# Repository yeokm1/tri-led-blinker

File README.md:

# tri-led-blinker

A "simple" blinking gift for somebody. Has On-Off switch and a button to change the order of blinking.

Blink orders:

1. Forward
2. Reverse
3. Twice forward
4. Twice reverse
5. All

##Software

1. Arduino 1.6.5 IDE
2. [Custom Lowpower library to support ATTiny85 by johnnie502](https://github.com/johnnie502/Low-Power/)

##Hardware

##Prototype

Front view with all LEDs lit

Back view

###Demo video on Youtube

###Parts used that are different from PCB design
1. [Adafruit LED Sequin (Ruby Red)](https://www.adafruit.com/products/1755)
2. [Adafruit LED Sequin (Emerald Green)](https://www.adafruit.com/products/1756)
3. [Adafruit LED Sequin (Royal Blue)](https://www.adafruit.com/products/1757)
4. [Adafruit USB Micro-B Breakout Board](https://www.adafruit.com/products/1833)
5. [Adafruit Perma-Proto Half-sized Breadboard PCB - Single](https://www.adafruit.com/products/1609)

## Proposed PCB Design

###PCB Design software and addons used

1. Eagle 7.3.0: I use Standard but Light should still be able to open/modify the files.
2. Seeed OPL libraries: Button, Connector, Diode (in pcb libraries folder)
2. Seeedstudio Design Rule Check for 2 layers (in repo as `SeeedStudio_2layer_DRU_no_angle_20140221.dru`)
3. Seeed Gerber Generater 2-layer board (in repo as `Seeed_Gerber_Generater_2-layer.cam`)

###Schematic drawings

Images are exported from Eagle at 600dpi.

The copper pour is connected to ground

###Parts required

1. JP1 and JP2: Pin header stand-in for [Adafruit Trinket 3V](https://www.adafruit.com/products/1500)
2. J1: SMD Micro-USB connector: Seeed OPL part 3400150P1
3. S1: [SPDT slide switch from Adafruit](https://www.adafruit.com/products/805). Others will work too
4. K1: Push button: Seeed OPL part 3110040P1
5. JP3 and JP4: Pin header stand-in for [Adafruit Pro Trinket LiIon/LiPoly Backpack Add-On](https://www.adafruit.com/products/2124)
6. D1: 0603 SMD Diffused-Red LED 1.7V-2.2V, 25mA: Seeed OPL part 0330020P1
7. D2: 0603 SMD Clear-Green LED 2.75V-3.95V , 25mA: Seeed OPL part 0330010P1
8. D2: 0603 SMD Clear-Blue LED 2.5V-3.1V , 25mA: Seeed OPL part 0330060P1
9. R1: Through-hole resistor 0.25W for red LED : Undetermined
10. R2: Through-hole resistor 0.25W for green LED : Undetermined
11. R3: Through-hole resistor 0.25W for blue LED : Undetermined

###PCB fabrication

PCB fabrication is currently done by [Seeedstudio](https://www.seeedstudio.com/service/index.php?r=pcb) based on the following settings. Remember to consult the [order submission guidelines](http://support.seeedstudio.com/knowledgebase/articles/422482-fusion-pcb-order-submission-guidelines) before submitting. Use the provided Gerber generator to produce the Gerber files.

Seeedstudio requires the following gerber files to be zipped up for submission:

1. Top Layer: pcbname.GTL
2. Top Solder Mask: pcbname.GTS
3. Top Silkscreen: pcbname.GTO
4. Bottom Layer: pcbname.GBL
5. Bottom Solder Mask﻿: pcbname.GBS
6. Bottom silkscreen: pcbname.GBO
7. Board Outline:pcbname.GML/GKO
8. Drills: pcbname.TXT
9. Inner Layer: pcbname.GL2(for 4 layer)
10. Inner Layer: pcbname.GL3(for 4 layer)

The zip file has been uploaded to the Releases section.

####My Fabrication Settings: 

1. Layer: 2
2. PCB Dimension: 5cm Max * 10cm Max
3. PCB Thickness: 1.2mm
4. PCB Qty: 10
5. PCB Color: Black (+US$20, expensive but I like Black)
6. Surface Finish: Hasl(Lead Free)
7. Copper weight: 1oz
8. Panalized PCBs: 1
9. Expedited Option: No
10. PCB Stencil: Unchecked

####PCB assembly:

Just use the provided `BOM File for Seeedstudio.csv`. I opted to do the assembly for only 5 pieces in case there are issues and I have to solder myself.

###Letters
I 3D-printed the letters based on the STL files obtained from [thingverse](http://www.thingiverse.com/thing:15198).

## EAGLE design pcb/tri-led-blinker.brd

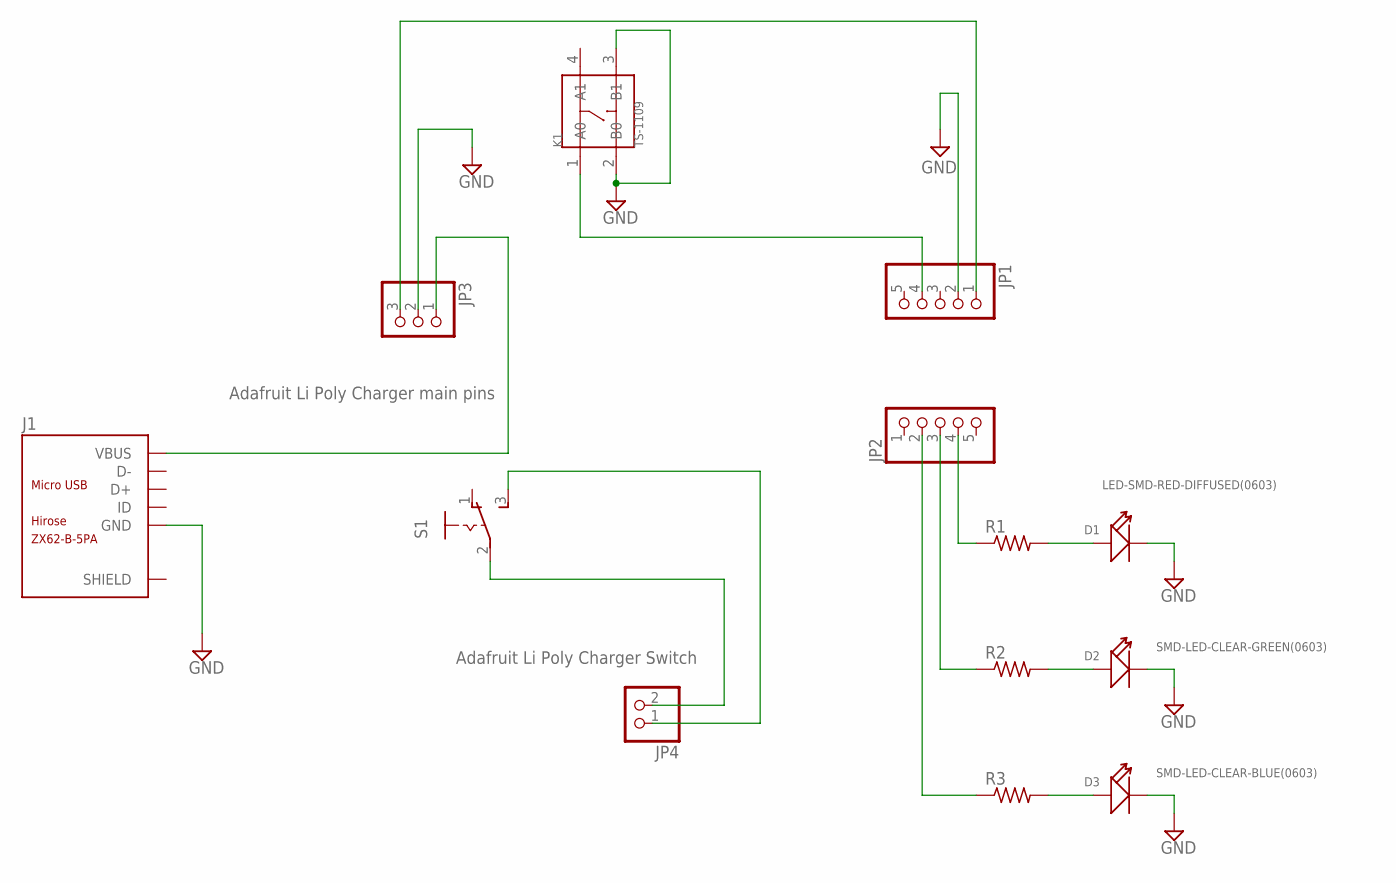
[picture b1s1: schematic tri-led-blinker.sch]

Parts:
D1: LED-SMD-RED-DIFFUSED(0603); LED-0603
D2: SMD-LED-CLEAR-GREEN(0603); LED-0603
D3: SMD-LED-CLEAR-BLUE(0603); LED-0603
J1: MICRO-USB-SMD(ZX62-B-5PA); MICRO-USB5+6P-SMD-0.65-AB
JP1, JP2: PINHD-1X5; 1X05
JP3: Adafruit Li Poly Charger main pins; 1X03
JP4: Adafruit Li Poly Charger Switch; 1X02
K1: TS-1109; SW4-6.0X6.0X5.0MM
R1, R2, R3: R-US_0207/7; 0207/7
S1: M251

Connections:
GND: D1.-, D2.-, D3.-, J1.5 (GND), JP1.2, JP3.2, K1.2 (B0), K1.3 (B1)
unnamed: D1.+, R1.2
unnamed: JP4.2, S1.2
unnamed: JP4.1, S1.3 (S)
unnamed: D2.+, R2.2
unnamed: JP1.4, K1.1 (A0)
unnamed: JP2.2, R3.1
unnamed: D3.+, R3.2
unnamed: JP2.4, R1.1
unnamed: JP1.1, JP3.3
unnamed: JP2.3, R2.1
VBUS: J1.1 (VBUS), JP3.1

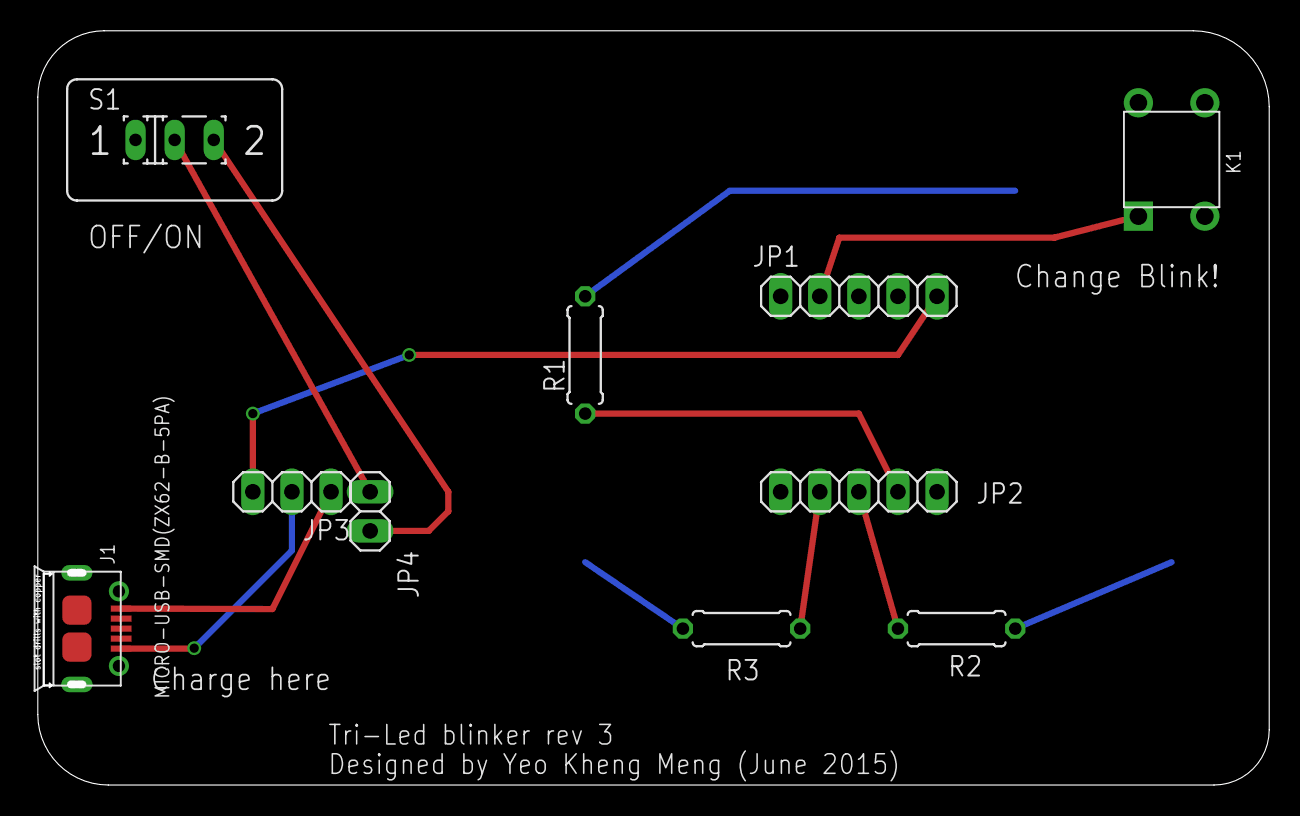
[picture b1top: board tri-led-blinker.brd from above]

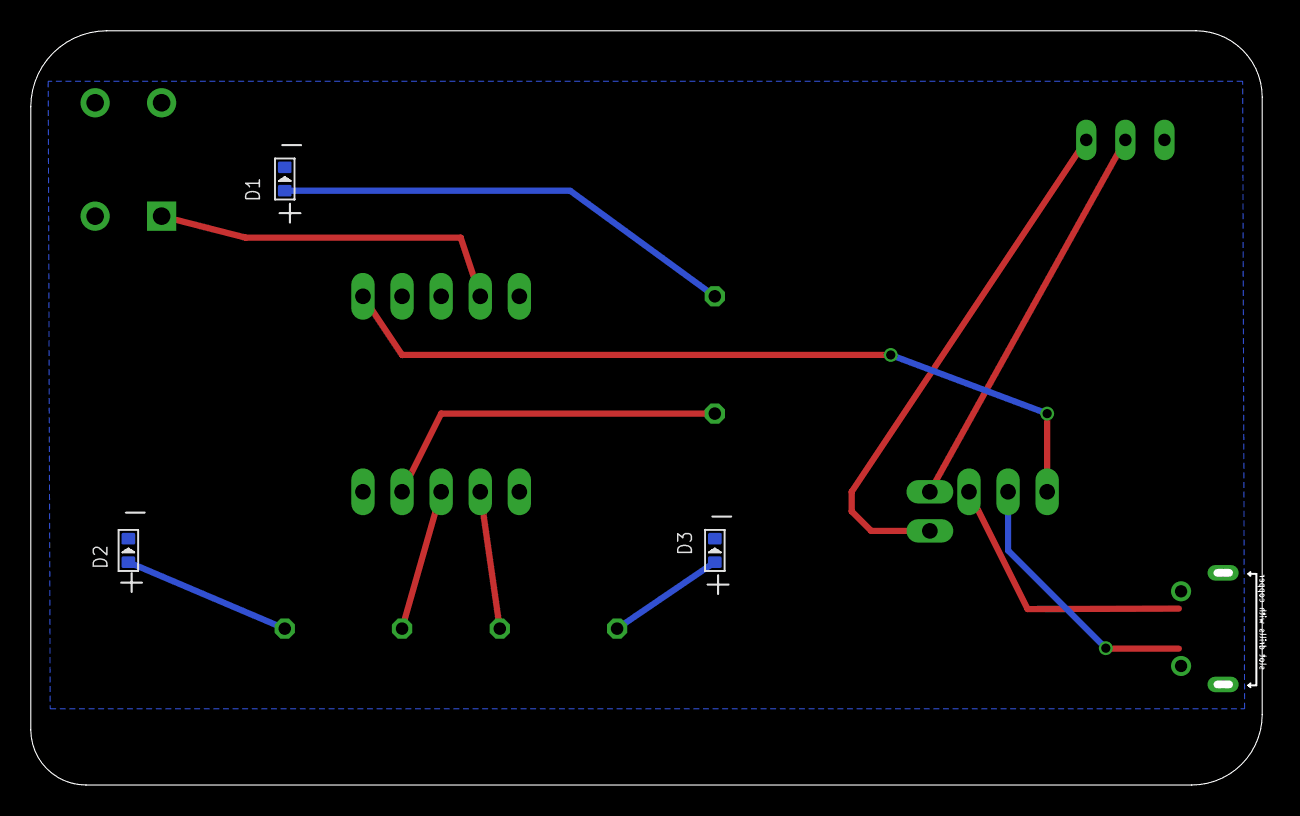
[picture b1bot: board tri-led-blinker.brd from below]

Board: 2 copper layers, 80.0 x 49.0 mm, 13 parts (3 on the bottom side), 12 nets.

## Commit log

2015-06-01 update air wire usb ground
2015-06-01 diode library
2015-06-01 added + and - labels to diode
2015-06-01 ratsnest
2015-06-01 bom file
2015-06-01 shift resistor r1 a bit to the left
2015-06-01 git ignore
2015-06-01 schematic size
2015-06-01 images
2015-06-01 seedstudio bom
2015-06-03 revision 2 add date
2015-06-19 working version
2015-06-19 state blink twice forward
2015-06-19 blink twice backward
2015-06-19 change button input pin to PB3
2015-06-19 use modified low power library
2015-06-19 gitattributes
2015-06-19 up rev to 3.
2015-06-19 ability to skip reverse states using #ifdef
2015-06-19 remove delay 10
2015-06-27 change 320010015-SMD to 320010006-DIP
